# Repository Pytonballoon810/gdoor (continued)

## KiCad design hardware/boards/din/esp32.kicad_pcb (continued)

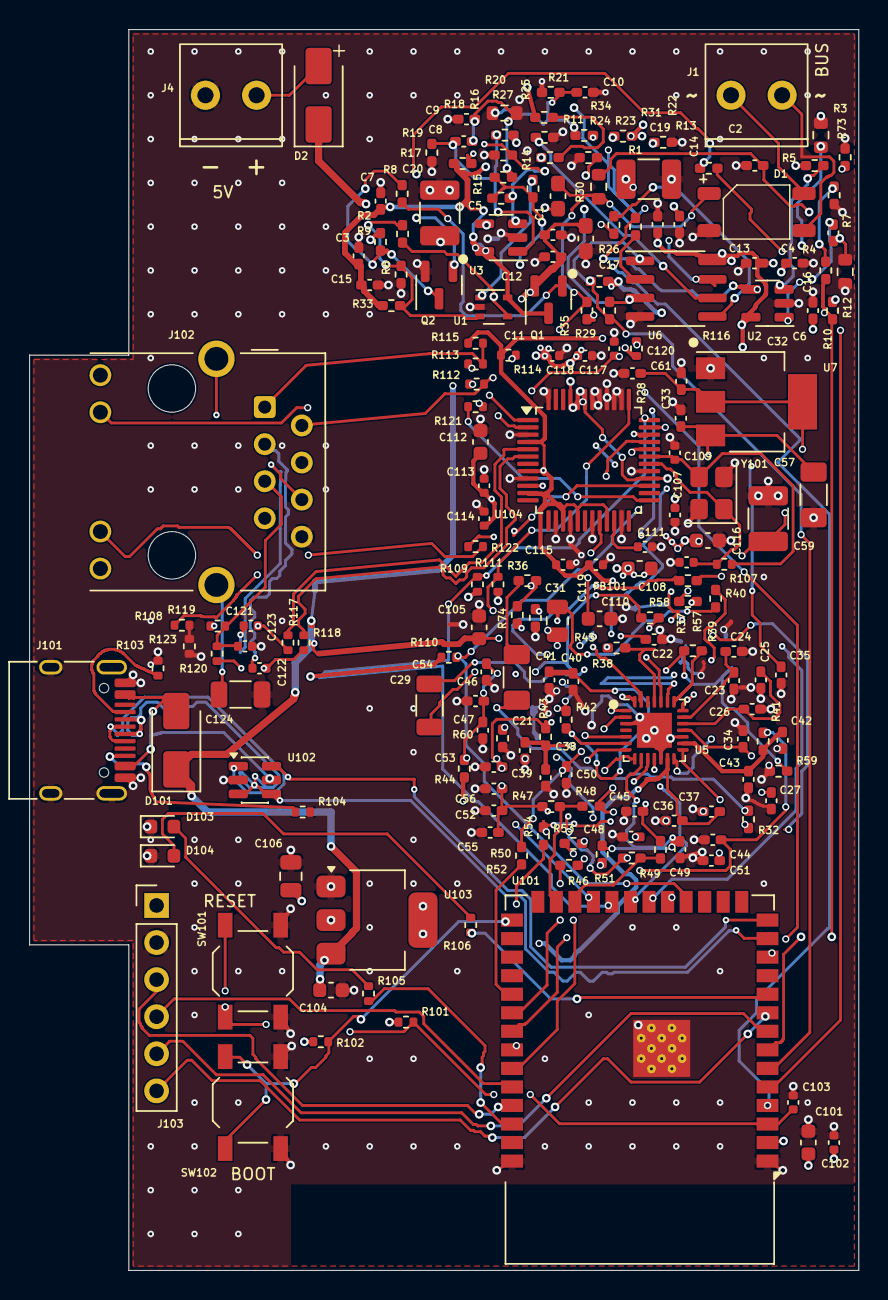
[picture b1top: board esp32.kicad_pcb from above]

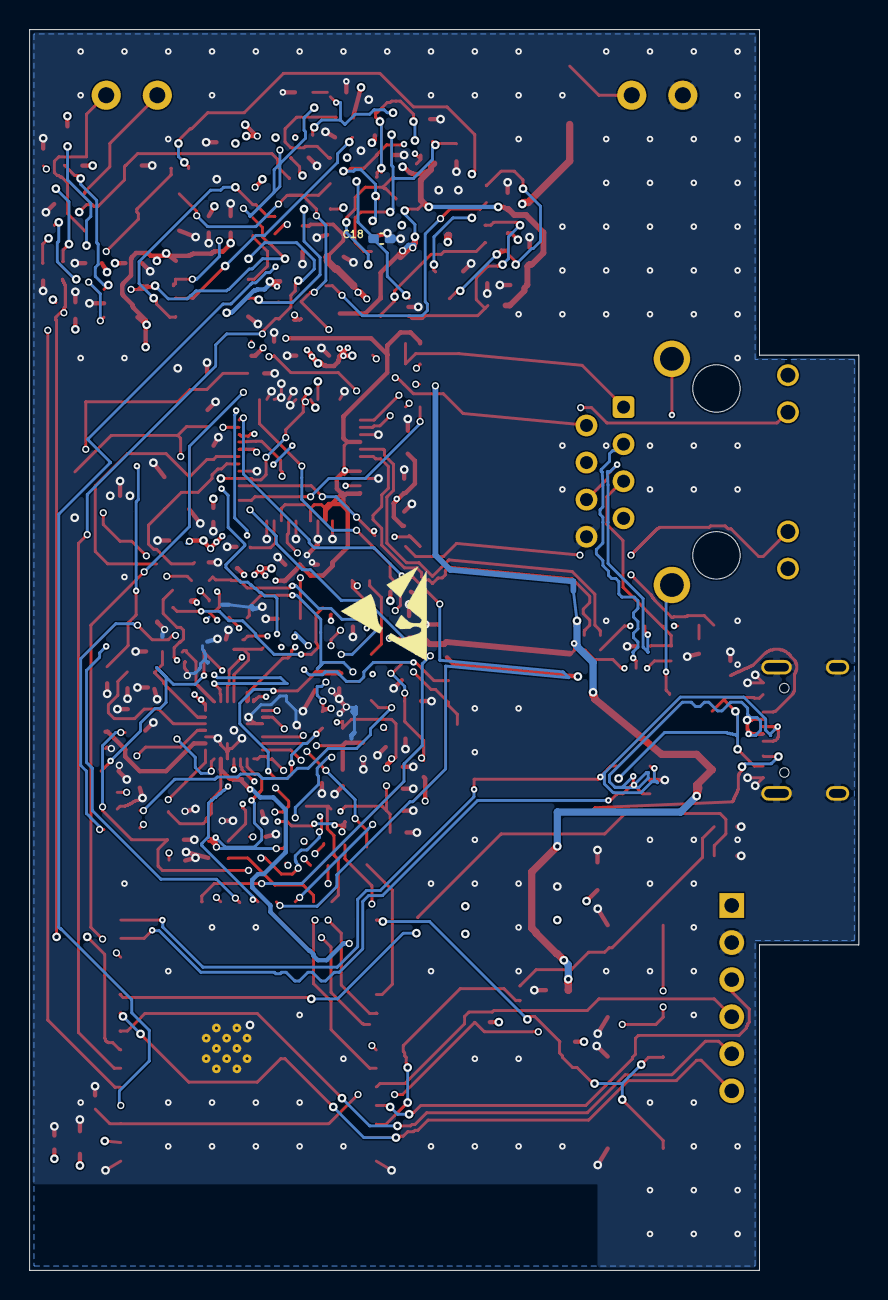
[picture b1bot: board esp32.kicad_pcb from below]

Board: 4 copper layers, 56.8 x 85.0 mm, 191 parts (2 on the bottom side), 116 nets.

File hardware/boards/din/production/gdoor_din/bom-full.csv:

Comment,Designator,Footprint,LCSC Part #
47n,C1,0603,C1622
1n,C10,0402,C1523
10u,"C101, C104, C105, C112, C116",0603,C19702
100n,"C22, C24, C26, C32, C33, C34, C102, C107, C114, C115, C117, C118, C119",0402,C1525
1u,"C103, C113",0402,C52923
22u,C106,0805,C45783
15p,"C108, C109",0402,C1548
100n,"C3, C5, C6, C7, C11, C13, C15, C16, C17, C36, C38, C40, C42, C46, C51, C53, C55",0402,C307331
4.7u,C110,0603,C19666
10n,"C111, C123",0402,C15195
10u,C12,0603,C96446
22n,C120,0402,C1532
6.8n,"C121, C122",0402,C1542
1n 2kV,C124,1206,C9196
10u,"C14, C23, C25, C27, C35, C37, C39, C41, C43, C47, C52, C54, C56",0402,C15525
100u,"C19, C20, C59",1210,C23742
100p,"C2, C4, C8, C9",0402,C1546
10u,"C21, C29, C57",1206,C13585
10u,C31,0805,C440198
22p,"C44, C45, C48, C49, C50, C61",0402,C1555
MB10S,D1,SOIC-4_4.55x3.7mm_P2.54mm,C2488
SS14,"D2, D101",D_SMA,C2480
red,"D103, D104",0603,C2286
120R@100MHz,FB101,0603,C14709
PlugIn_Terminal_Screw,"J1, J4",anschlussklemme2x1_3_5,C695629
USB-C,J101,USB_C_Receptacle_HRO_TYPE-C-31-M-12,C165948
HY911105AE,J102,RJ45_Hanrun_HR911105A_Horizontal,C69427
EXP,J103,PinHeader_1x06_P2.54mm_Vertical,C37208
MMBT5401,Q1,SOT-23,C8326
MMBT2222A,Q2,SOT-23,C8512
130k,"R1, R20",0603,C22795
18k,"R6, R10, R15, R22, R27, R33",0402,C25762
10k,"R8, R11, R13, R23, R24, R29, R31, R45, R73, R101, R102, R108",0402,C25744
5.1k,"R5, R7, R16, R17, R103, R104",0402,C25905
1k,"R14, R37, R38, R39, R40, R105, R106",0402,C11702
1M,R107,0402,C26083
4.7k,"R21, R26, R109, R110, R111",0402,C25900
0,"R34, R36, R57, R58, R59, R60, R74, R112, R113, R117, R118",0402,C17168
49.9 1%,"R114, R115, R119, R120",0402,C25120
10,R116,0402,C25077
2k4,"R12, R25, R46, R47, R123",0402,C25882
330,"R121, R122",0402,C25104
100k,"R18, R19, R35",0402,C25741
22k,R2,0402,C25768
47k,"R9, R28, R30",0402,C25792
82k,"R3, R4",0603,C23254
22,R32,0402,C25092
33,"R41, R42, R43, R44, R50, R51, R52, R53, R54",0402,C25105
100,"R48, R49",0402,C25076
TL3342,"SW101, SW102",SW_SPST_TL3342,C318884
TLV9351,U1,SOT-353_SC-70-5,C4367425
ESP32-S3-WROOM-1-N8R2,U101,ESP32-S3-WROOM-1,C2913204
USBLC6-2SC6,U102,SOT-23-6,C2687116
AP2114H-3.3TRG1,U103,SOT-223-3_TabPin2,C150716
W5500,U104,LQFP-48_7x7mm_P0.5mm,C32843
LMV321,"U2, U3",SOT-23-5,C7972
ES8374,U5,QFN-28-1EP_4x4mm_P0.45mm_EP2.4x2.4mm,C365738
LM393,U6,SOIC-8_3.9x4.9mm_P1.27mm,C7955
AMS1117-3.3,U7,SOT-223-3_TabPin2,C6186
25MHz,Y101,Crystal_SMD_3225-4Pin_3.2x2.5mm,C9006
